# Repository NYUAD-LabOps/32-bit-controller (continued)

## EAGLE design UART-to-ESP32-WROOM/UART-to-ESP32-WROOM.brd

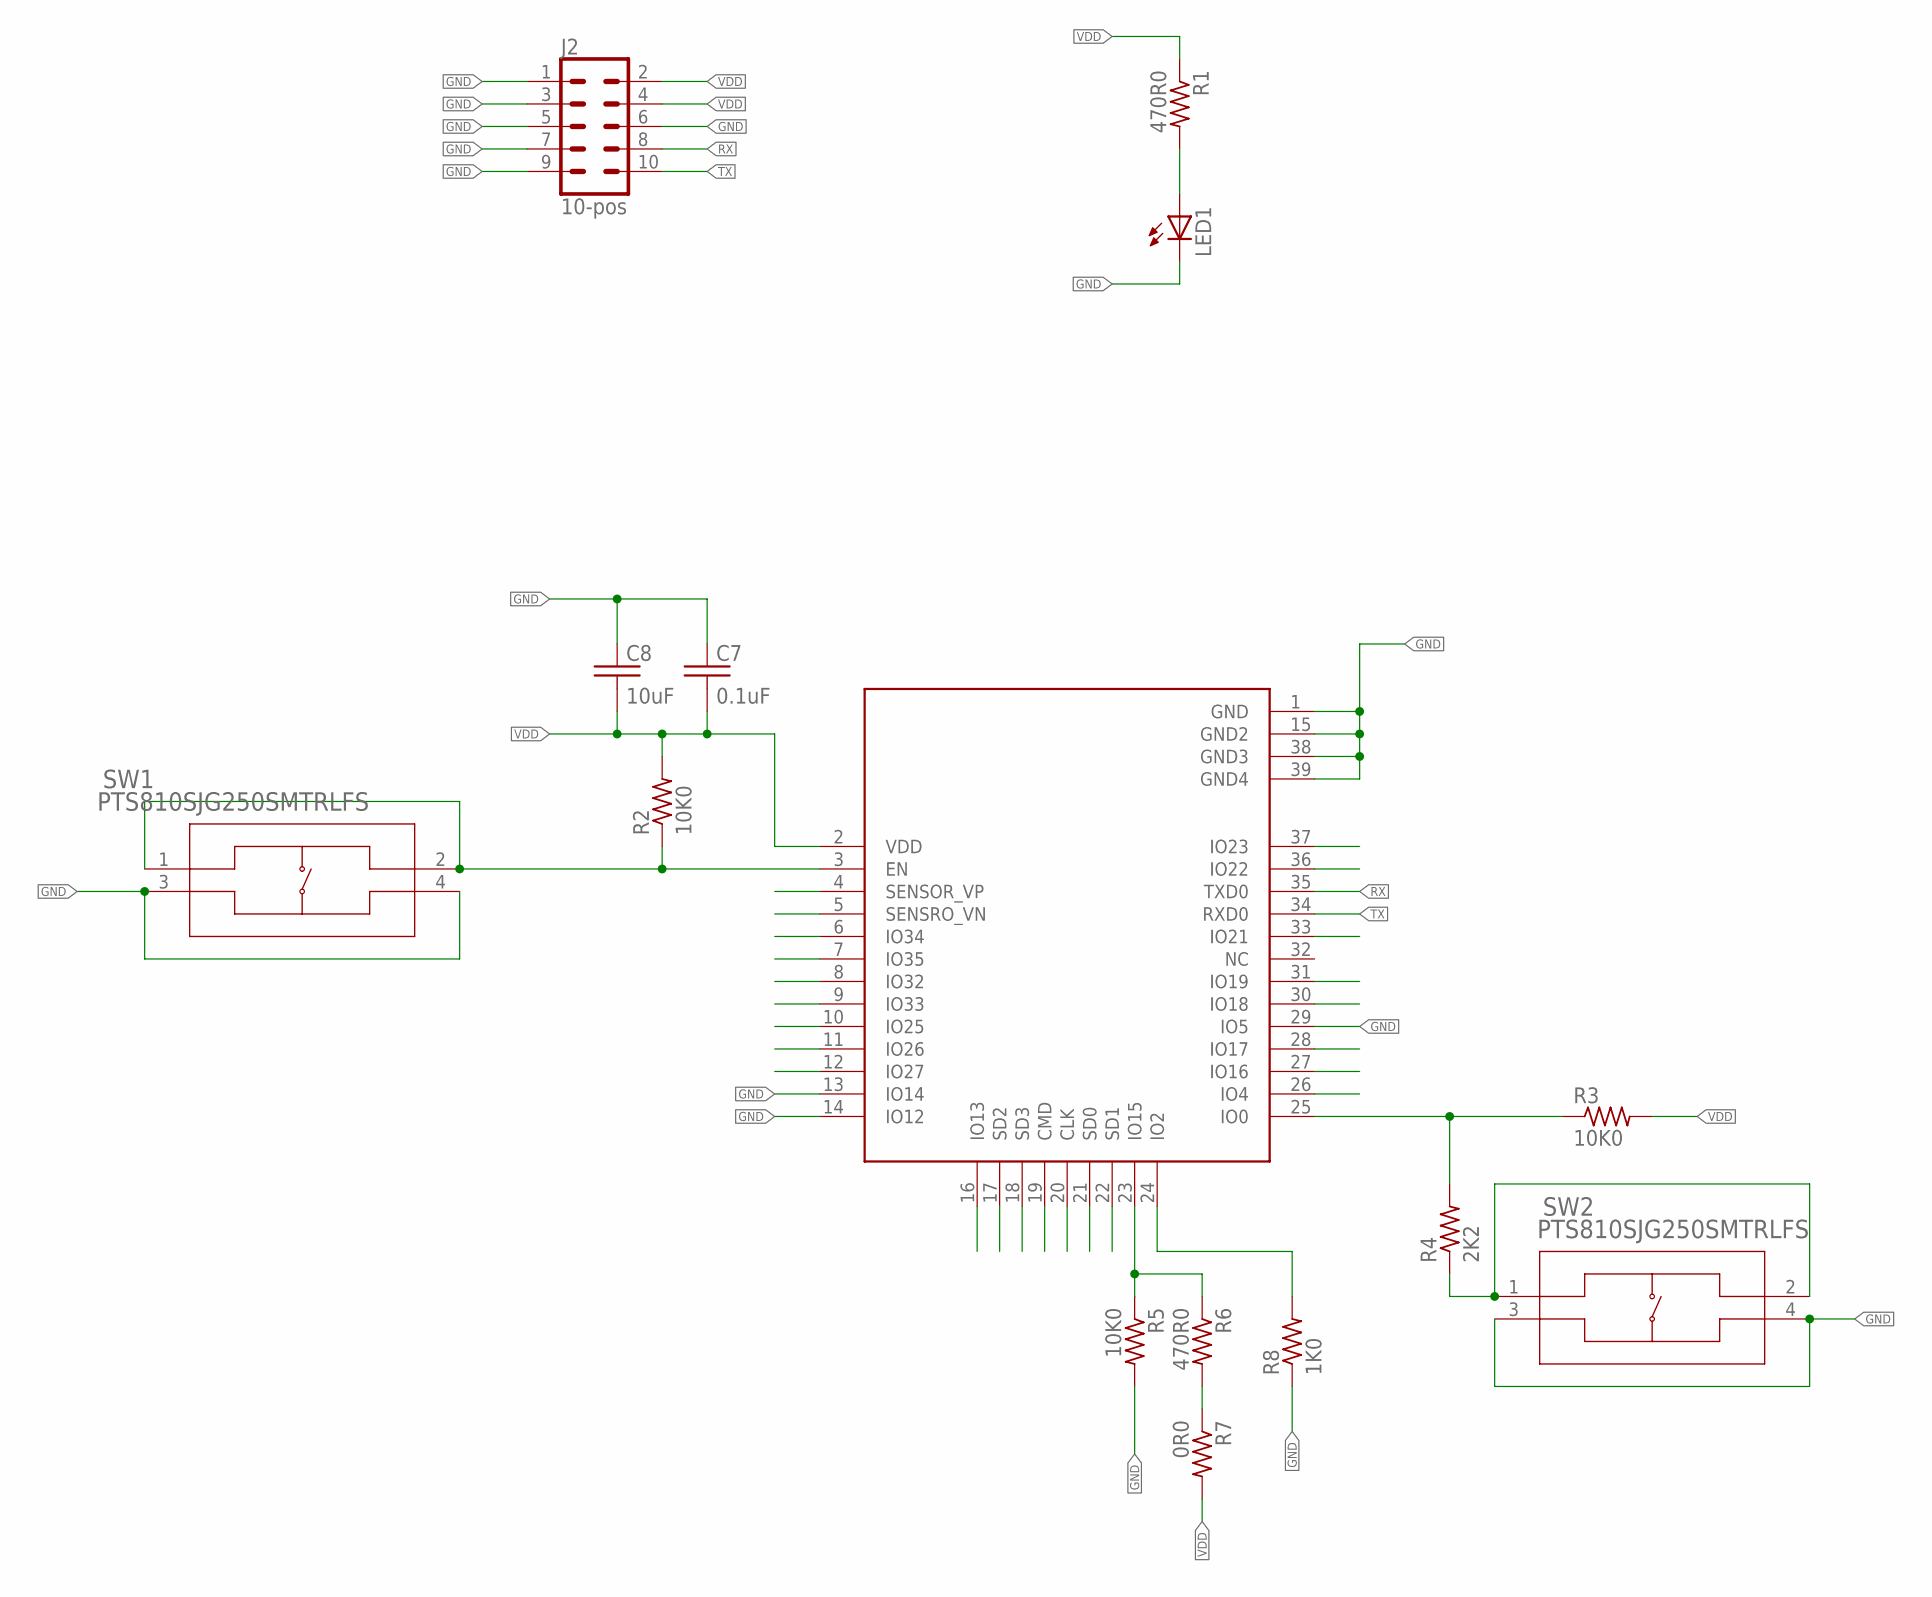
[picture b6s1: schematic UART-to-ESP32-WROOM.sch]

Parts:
C7: 0.1uF; 0402
C8: 10uF; 0402
J2: 10-pos; 2X5
LED1: Green; LED_0805_GREEN
R1, R6: 470R0; 0402
R2, R3, R5: 10K0; 0402
R4: 2K2; 0402
R7: 0R0; 0402
R8: 1K0; 0402
SW1, SW2: PTS810SJG250SMTRLFS; PTS810
U2: ESP32-WROOM-32D

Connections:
CHIP_PU: R2.P$1 (1), SW1.1, SW1.2, U2.3 (EN)
GND: C7.P$1 (1), C8.P$1 (1), J2.1, J2.3, J2.5, J2.6, J2.7, J2.9, LED1.C, R5.P$2 (2), R8.P$1 (1), SW1.3, SW1.4, SW2.3, SW2.4, U2.1 (GND), U2.13 (IO14), U2.14 (IO12), U2.15 (GND2), U2.29 (IO5), U2.38 (GND3), U2.39 (GND4)
unnamed: LED1.A, R1.P$2 (2)
unnamed: R5.P$1 (1), R6.P$1 (1), U2.23 (IO15)
unnamed: R4.P$1 (1), SW2.1, SW2.2
unnamed: R6.P$2 (2), R7.P$1 (1)
unnamed: R8.P$2 (2), U2.24 (IO2)
unnamed: R3.P$1 (1), R4.P$2 (2), U2.25 (IO0)
RX: J2.8, U2.35 (TXD0)
TX: J2.10, U2.34 (RXD0)
VDD: C7.P$2 (2), C8.P$2 (2), J2.2, J2.4, R1.P$1 (1), R2.P$2 (2), R3.P$2 (2), R7.P$2 (2), U2.2 (VDD)

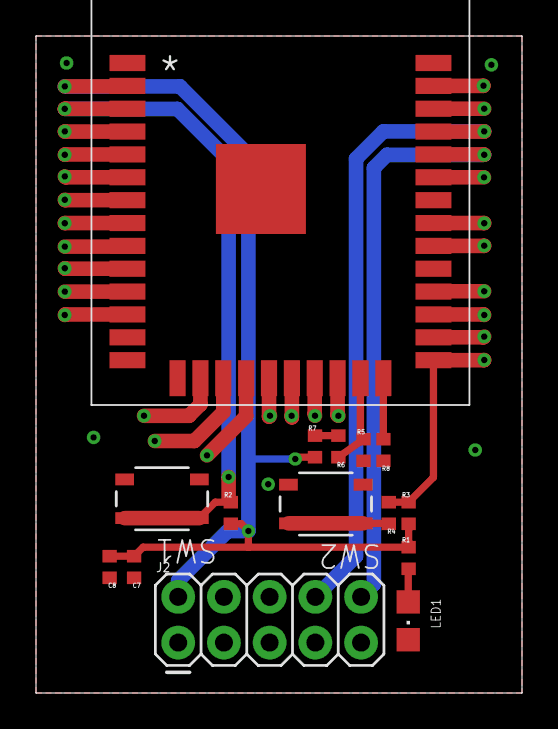
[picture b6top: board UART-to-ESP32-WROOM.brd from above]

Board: 2 copper layers, 27.0 x 36.5 mm, 15 parts (0 on the bottom side), 11 nets.

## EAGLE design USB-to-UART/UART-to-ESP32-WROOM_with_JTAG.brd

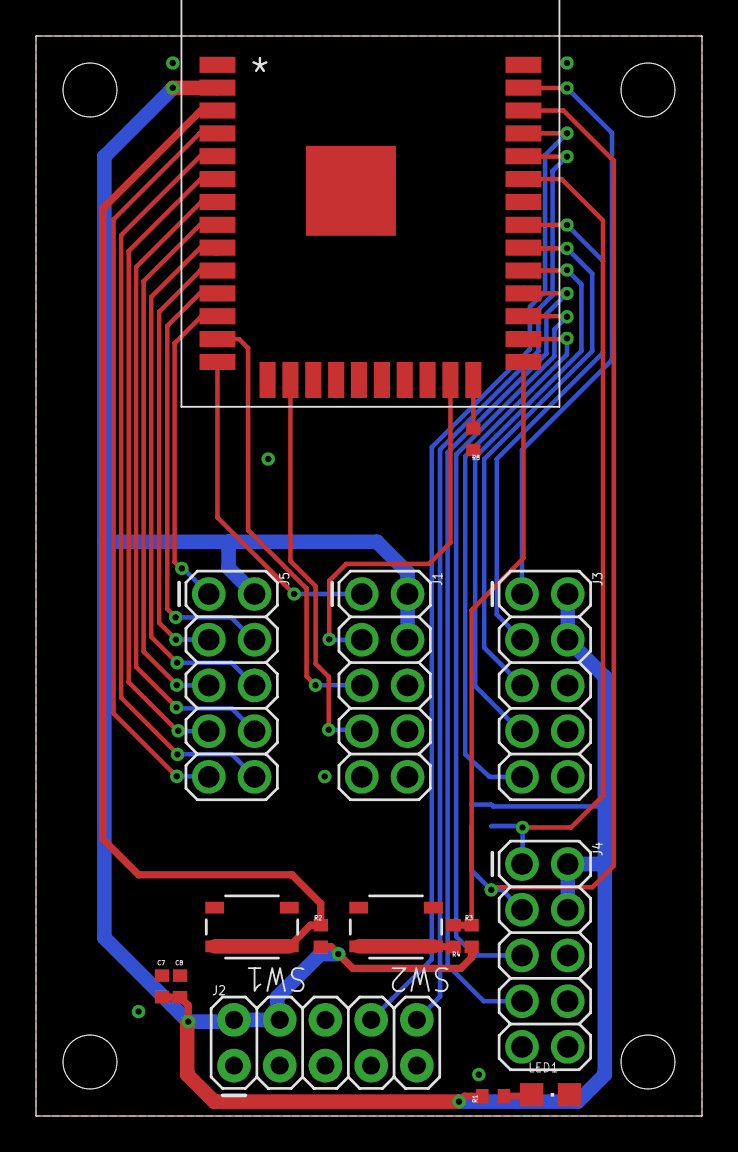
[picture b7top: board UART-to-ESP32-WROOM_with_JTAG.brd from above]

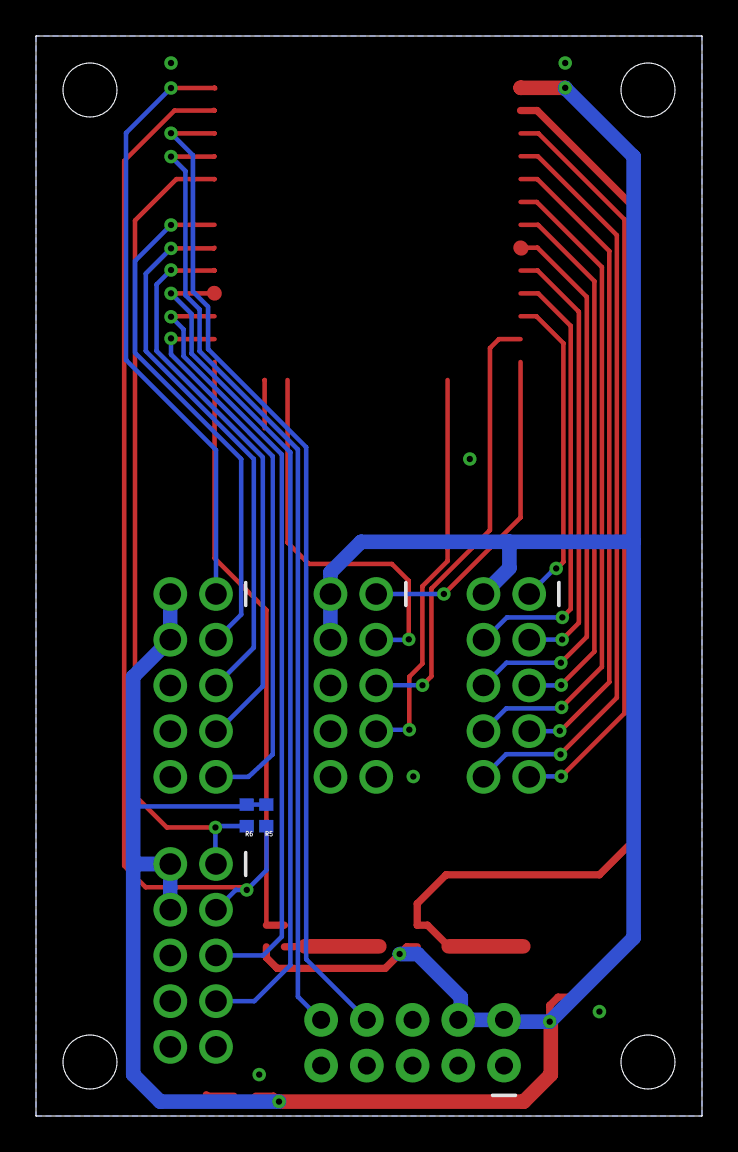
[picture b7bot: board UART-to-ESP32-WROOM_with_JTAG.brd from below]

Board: 2 copper layers, 37.0 x 60.0 mm, 18 parts (2 on the bottom side), 31 nets.

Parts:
C7: 0.1uF; 0402
C8: 10uF; 0402
J1, J3, J4, J5: 2X5
J2: 10-pos; 2X5@1
LED1: Green; LED_0805_GREEN
R1: 470R0; 0402
R2, R3, R5, R6: 10K0; 0402
R4: 2K2; 0402
R8: 1K0; 0402
SW1, SW2: PTS810SJG250SMTRLFS; PTS810
U2: ESP32-WROOM-32D

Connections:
CHIP_PU: R2.P$1, SW1.1, SW1.2, U2.3
GND: C7.P$1, C8.P$1, J1.6, J1.8, J1.10, J2.1, J2.3, J2.5, J2.6, J2.7, J2.9, J3.6, J3.8, J3.10, J4.6, J4.8, J4.10, LED1.C, R8.P$1, SW1.3, SW1.4, SW2.3, SW2.4, U2.1, U2.15, U2.38, U2.39
I2C_SCL: J4.3, R5.P$1, U2.36
I2C_SDA: J4.1, R6.P$1, U2.33
IO25: J5.3, U2.10
IO26: J5.4, U2.11
IO27: J5.1, U2.12
IO32: J5.5, U2.8
IO33: J5.6, U2.9
IO34: J5.7, U2.6
IO35: J5.8, U2.7
unnamed: LED1.A, R1.P$2
unnamed: R4.P$1, SW2.1, SW2.2
unnamed: R8.P$2, U2.24
unnamed: R3.P$1, R4.P$2, U2.25
RX: J2.10, U2.34
RX2: J4.5, U2.27
SENSORVN: J5.10, U2.5
SENSORVP: J5.9, U2.4
SPI_CLK: J3.5, U2.30
SPI_CS0: J3.7, U2.29
SPI_CS1: J3.9, U2.26
SPI_MISO: J3.3, U2.31
SPI_MOSI: J3.1, U2.37
TCK: J1.7, U2.16
TDI: J1.1, U2.14
TDO: J1.3, U2.23
TMS: J1.5, U2.13
TX: J2.8, U2.35
TX2: J4.7, U2.28
VDD: C7.P$2, C8.P$2, J1.2, J1.4, J2.2, J2.4, J3.2, J3.4, J4.2, J4.4, J5.2, R1.P$1, R2.P$2, R3.P$2, R5.P$2, R6.P$2, U2.2
